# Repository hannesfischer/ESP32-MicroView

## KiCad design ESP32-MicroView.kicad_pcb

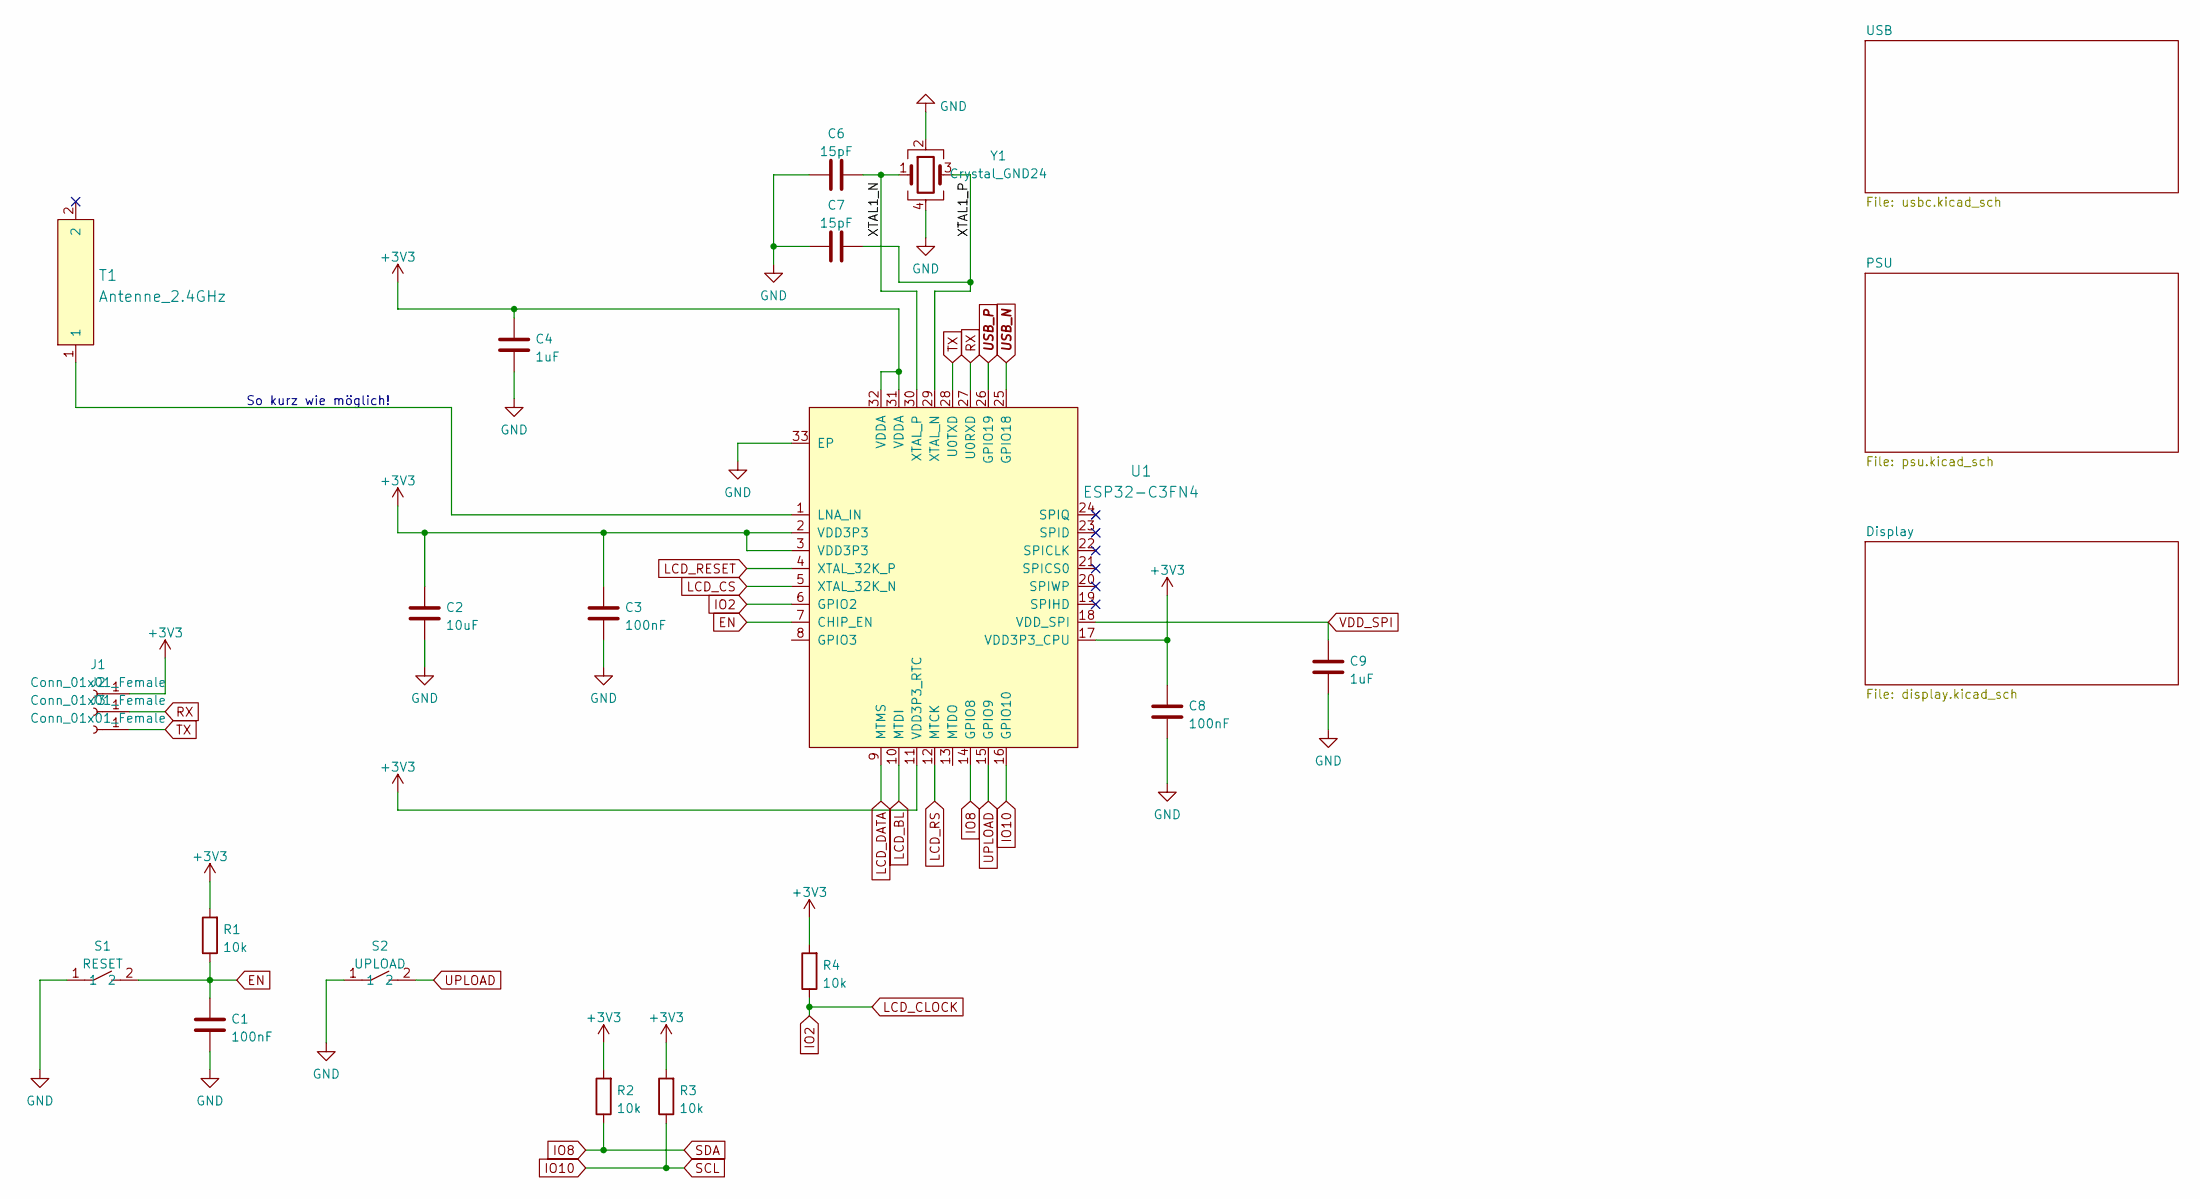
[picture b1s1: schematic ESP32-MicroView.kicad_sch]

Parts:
C1, C3, C8: 100nF; C_0402_1005Metric
C2: 10uF; C_0402_1005Metric
C4, C9: 1uF; C_0603_1608Metric
C6, C7: 15pF; C_0603_1608Metric
J1, J2, J3: Conn_01x01_Female; TestPoint_Pad_D1.0mm
R1, R2, R3, R4: 10k; R_0402_1005Metric
S1: RESET; SMD_Taster_Seitenbetaetigt
S2: UPLOAD; SMD_Taster_Seitenbetaetigt
T1: Antenne_2.4GHz; LCSC Part C293767
U1: ESP32-C3FN4; QFN-32-1EP_5x5mm_P0.5mm_EP3.7x3.7mm; LCSC Part C2848860
Y1: Crystal_GND24; Crystal_SMD_3225-4Pin_3.2x2.5mm

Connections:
+3V3: C2.1, C3.1, C4.1, C8.1, J1.1, R1.2, R2.2, R3.2, R4.2, U1.2 (VDD3P3), U1.3 (VDD3P3), U1.11 (VDD3P3_RTC), U1.17 (VDD3P3_CPU), U1.31 (VDDA), U1.32 (VDDA); also elsewhere on the board
/XTAL1_N: C6.2, U1.30 (XTAL_P), Y1.1
/XTAL1_P: C7.2, U1.29 (XTAL_N), Y1.3
EN: C1.1, R1.1, S1.2, U1.7 (CHIP_EN)
GND: C1.2, C2.2, C3.2, C4.2, C6.1, C7.1, C8.2, C9.2, S1.1, S2.1, U1.33 (EP), Y1.2, Y1.4; also elsewhere on the board
IO2: R4.1, U1.6 (GPIO2); also elsewhere on the board
IO8: R2.1, U1.14 (GPIO8)
IO10: R3.1, U1.16 (GPIO10)
LCD_BL: U1.10 (MTDI); also elsewhere on the board
LCD_CS: U1.5 (XTAL_32K_N); also elsewhere on the board
LCD_DATA: U1.9 (MTMS); also elsewhere on the board
LCD_RESET: U1.4 (XTAL_32K_P); also elsewhere on the board
LCD_RS: U1.12 (MTCK); also elsewhere on the board
unnamed: T1.1, U1.1 (LNA_IN)
RX: J2.1, U1.27 (U0RXD)
TX: J3.1, U1.28 (U0TXD)
UPLOAD: S2.2, U1.15 (GPIO9)
USB_N: U1.25 (GPIO18); also elsewhere on the board
USB_P: U1.26 (GPIO19); also elsewhere on the board
VDD_SPI: C9.1, U1.18 (VDD_SPI)

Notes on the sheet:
So kurz wie möglich!

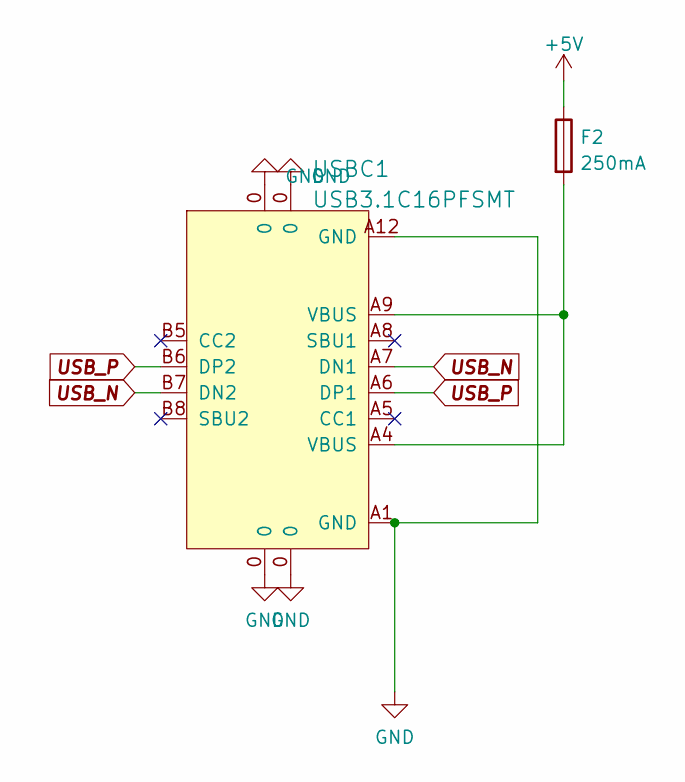
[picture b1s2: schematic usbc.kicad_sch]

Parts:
F2: 250mA; R_0603_1608Metric
USBC1: USB3.1C16PFSMT; USB-C-SMD_TYPE-C-USB-17; LCSC Part C167321

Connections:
+5V: F2.1; also elsewhere on the board
GND: USBC1.0, USBC1.A1 (GND), USBC1.A12 (GND); also elsewhere on the board
unnamed: F2.2, USBC1.A4 (VBUS), USBC1.A9 (VBUS)
USB_N: USBC1.A7 (DN1), USBC1.B7 (DN2); also elsewhere on the board
USB_P: USBC1.A6 (DP1), USBC1.B6 (DP2); also elsewhere on the board

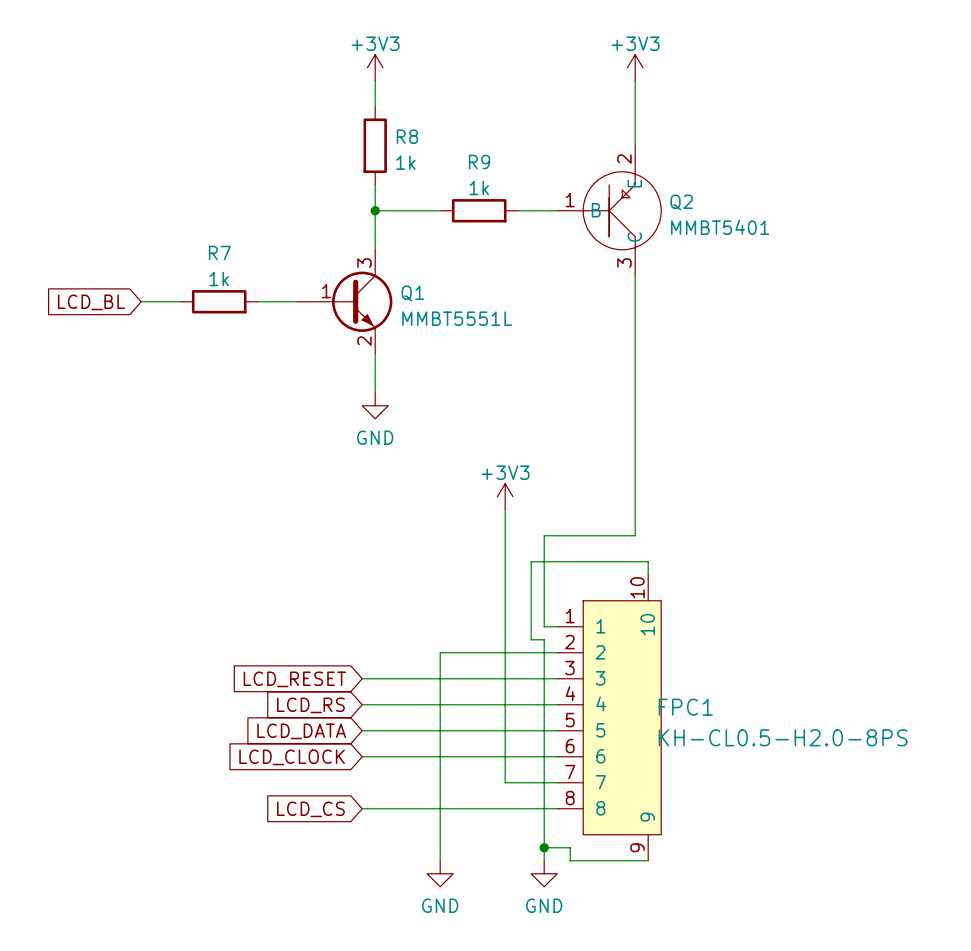
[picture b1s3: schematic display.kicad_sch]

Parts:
FPC1: KH-CL0.5-H2.0-8PS; ST7735_PCB_Connector; LCSC Part C262581
Q1: MMBT5551L; SOT-23
Q2: MMBT5401; SOT-23
R7, R8, R9: 1k; R_0402_1005Metric_Pad0.72x0.64mm_HandSolder

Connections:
+3V3: FPC1.7, Q2.2 (E), R8.1; also elsewhere on the board
GND: FPC1.2, FPC1.9, FPC1.10, Q1.2 (E); also elsewhere on the board
IO2: FPC1.6; also elsewhere on the board
LCD_BL: R7.1; also elsewhere on the board
LCD_CS: FPC1.8; also elsewhere on the board
LCD_DATA: FPC1.5; also elsewhere on the board
LCD_RESET: FPC1.3; also elsewhere on the board
LCD_RS: FPC1.4; also elsewhere on the board
unnamed: FPC1.1, Q2.3 (C)
unnamed: Q1.1 (B), R7.2
unnamed: Q1.3 (C), R8.2, R9.1
unnamed: Q2.1 (B), R9.2

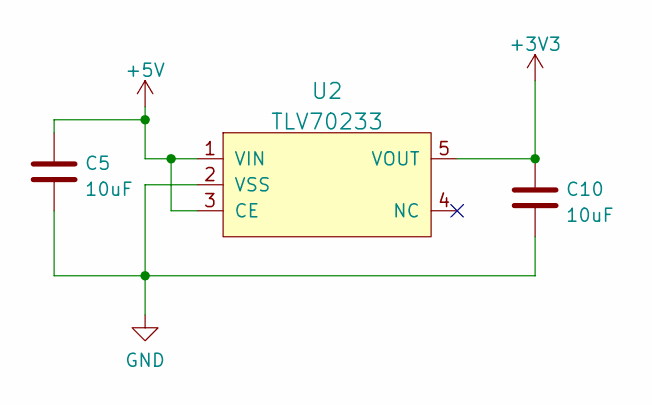
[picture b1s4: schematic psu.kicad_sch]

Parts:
C5, C10: 10uF; C_0402_1005Metric
U2: TLV70233; SOT-23-5; LCSC Part C82942

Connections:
+3V3: C10.1, U2.5 (VOUT); also elsewhere on the board
+5V: C5.1, U2.1 (VIN), U2.3 (CE); also elsewhere on the board
GND: C5.2, C10.2, U2.2 (VSS); also elsewhere on the board

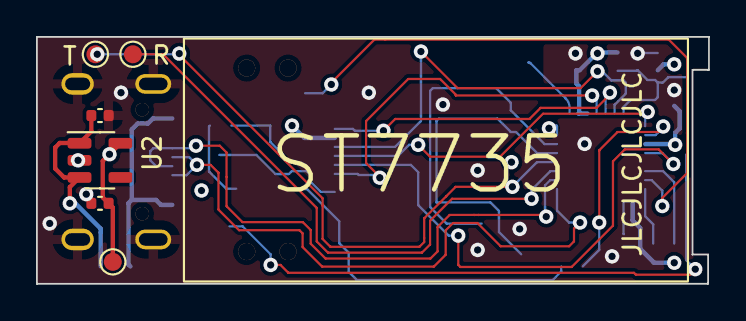
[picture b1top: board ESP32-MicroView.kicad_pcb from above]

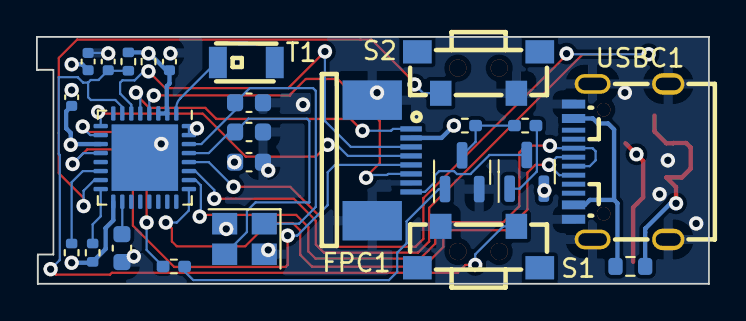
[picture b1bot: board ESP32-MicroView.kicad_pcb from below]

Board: 4 copper layers, 37.3 x 13.7 mm, 31 parts (24 on the bottom side), 26 nets.

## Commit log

2022-09-27 Initialized Repository
2022-09-27 added schematics.pdf
